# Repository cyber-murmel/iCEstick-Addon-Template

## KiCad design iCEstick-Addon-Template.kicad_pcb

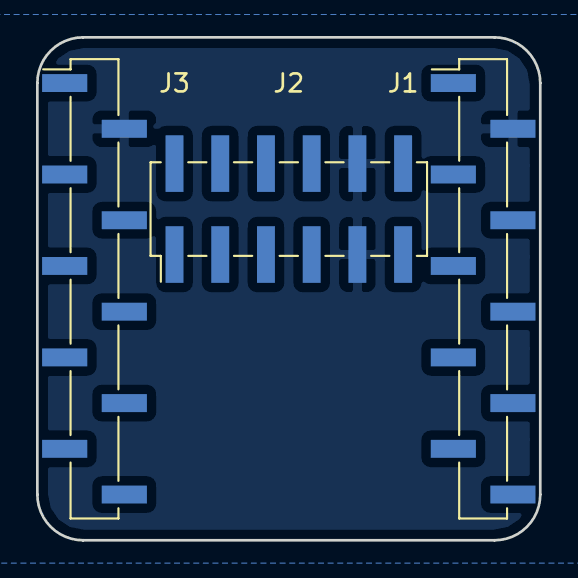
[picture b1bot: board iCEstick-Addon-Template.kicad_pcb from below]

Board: 2 copper layers, 27.9 x 27.9 mm, 3 parts (3 on the bottom side), 2 nets, no tracks yet.

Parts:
J1, J3: Conn_01x10; Pin_Header_Straight_1x10_Pitch2.54mm_SMD_Pin1Left
J2: PMOD; Pin_Header_Straight_2x06_Pitch2.54mm_SMD

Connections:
+3V3: J1.1, J2.11, J2.12, J3.1
GND: J1.2, J2.9, J2.10, J3.2

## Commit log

2018-01-10 adds meta direcotry
2018-01-10 WIP: untested initial schematic and pcb design
2018-01-10 changed bus labels; added info
2018-01-10 ignore cache lib
2018-01-11 made pin headers smd; removed 3v3 plane
